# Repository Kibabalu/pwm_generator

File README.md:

# PWM power output generator

PWM power output generator for utilization in training arangements.

Generates a 0 to 100% duty cycle to the load at the output. The dyty cycle can be controlled by an potentiometer. Operating voltage 12VDC. Max. current 3A. In addition it features Inverse supply voltage protection and over-voltage protection. The board fits into a Hammond 1593K enclosure.

Most of PWM generator designs are based on 555 ICs. But I haven't found a circuit that covers up the full range from 0 to 100% duty cycle. Thus I used a more basic design: A combination of a Schmitt trigger and a Integrator, both implemented with two opamps (TLV2372), is feeding a comparator (TLV2372). The duty cycle of the resulting PWM signal is determind by the switching voltage comming from a potentiometer. A complementary driver, made by a NPN (BC817) and a PNP (BC807) transistor, drives a MOSFET (TSM900n06CW) for the load.

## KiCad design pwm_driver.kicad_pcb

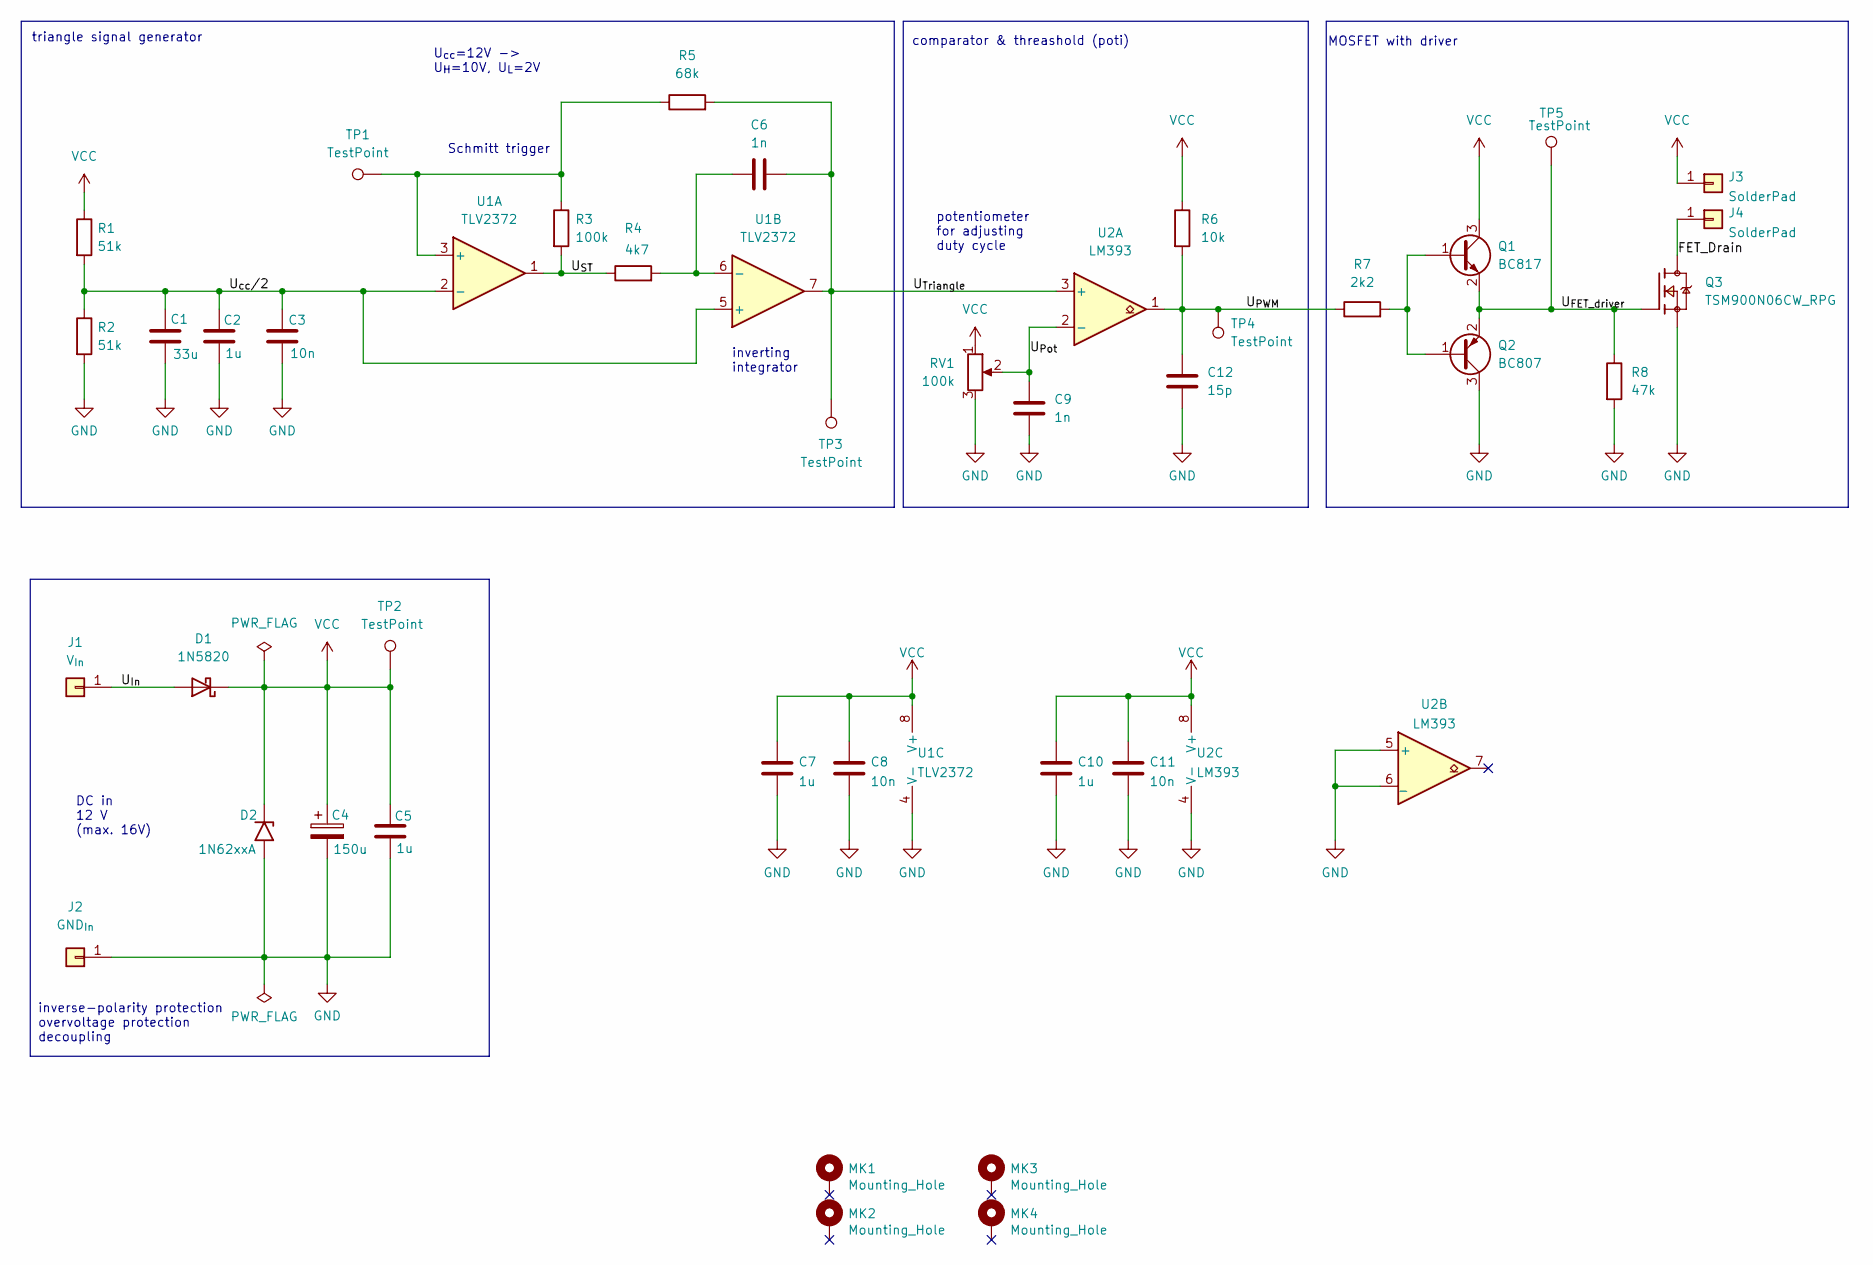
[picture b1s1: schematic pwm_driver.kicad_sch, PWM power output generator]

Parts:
C1: 33u; C_1206_3216Metric_Pad1.33x1.80mm_HandSolder
C2, C5, C7, C10: 1u; C_1206_3216Metric_Pad1.33x1.80mm_HandSolder
C3, C8, C11: 10n; C_1206_3216Metric_Pad1.33x1.80mm_HandSolder
C4: 150u; CP_Radial_D6.3mm_P2.50mm
C6, C9: 1n; C_1206_3216Metric_Pad1.33x1.80mm_HandSolder
C12: 15p; C_1206_3216Metric_Pad1.33x1.80mm_HandSolder
D1: 1N5820; D_DO-201AD_P15.24mm_Horizontal
D2: 1N62xxA; D_DO-201AE_P15.24mm_Horizontal
J1: V_{In}; SolderWirePad_1x01_SMD_5x10mm
J2: GND_{In}; SolderWirePad_1x01_SMD_5x10mm
J3, J4: SolderPad; SolderWirePad_1x01_SMD_5x10mm
MK1: Mounting_Hole; MountingHole_3.2mm_M3
MK2, MK3, MK4: Mounting_Hole; MountingHole_3.2mm_M3_ISO7380
Q1: BC817; SOT-23
Q2: BC807; SOT-23
Q3: TSM900N06CW_RPG; TRANS_TSM900N06CW_RPG; PARTREV D1706
R1, R2: 51k; R_1206_3216Metric_Pad1.30x1.75mm_HandSolder
R3: 100k; R_1206_3216Metric_Pad1.30x1.75mm_HandSolder
R4: 4k7; R_1206_3216Metric_Pad1.30x1.75mm_HandSolder
R5: 68k; R_1206_3216Metric_Pad1.30x1.75mm_HandSolder
R6: 10k; R_1206_3216Metric_Pad1.30x1.75mm_HandSolder
R7: 2k2; R_1206_3216Metric_Pad1.30x1.75mm_HandSolder
R8: 47k; R_1206_3216Metric_Pad1.30x1.75mm_HandSolder
RV1: 100k; PinHeader_1x03_P2.54mm_Vertical_SMD_Pin1Left
TP1, TP2, TP3, TP4, TP5: TestPoint; TestPoint_Pad_1.5x1.5mm
U1: TLV2372; SOIC-8_3.9x4.9mm_P1.27mm
U2: LM393; SOIC-8_3.9x4.9mm_P1.27mm

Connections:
/FET_Drain: J4.1, Q3.2, Q3.4
/U_{FET_driver}: Q1.2 (E), Q2.2 (E), Q3.1, R8.1, TP5.1
/U_{In}: D1.2 (A), J1.1
/U_{PWM}: C12.1, R6.2, R7.1, TP4.1, U2.1
/U_{Pot}: C9.1, RV1.2, U2.2 (-)
/U_{ST}: R3.2, R4.1, U1.1
/U_{Triangle}: C6.2, R5.2, TP3.1, U1.7, U2.3 (+)
/U_{cc}/2: C1.1, C2.1, C3.1, R1.2, R2.1, U1.2 (-), U1.5 (+)
GND: C1.2, C2.2, C3.2, C4.2, C5.2, C7.2, C8.2, C9.2, C10.2, C11.2, C12.2, D2.2 (A2), J2.1, Q2.3 (C), Q3.3, R2.2, R8.2, RV1.3, U1.4 (V-), U2.4 (V-), U2.5 (+), U2.6 (_)
unnamed: C6.1, R4.2, U1.6 (-)
unnamed: Q1.1 (B), Q2.1 (B), R7.2
unnamed: R3.1, R5.1, TP1.1, U1.3 (+)
VCC: C4.1, C5.1, C7.1, C8.1, C10.1, C11.1, D1.1 (K), D2.1 (A1), J3.1, Q1.3 (C), R1.1, R6.1, RV1.1, TP2.1, U1.8 (V+), U2.8 (V+)

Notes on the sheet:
Schmitt trigger
inverse-polarity protection overvoltage protection decoupling
comparator & threashold (poti)
U_{cc}=12V -> U_{H}=10V, U_{L}=2V
potentiometer for adjusting duty cycle
MOSFET with driver
triangle signal generator
DC in 12 V (max. 16V)
inverting integrator

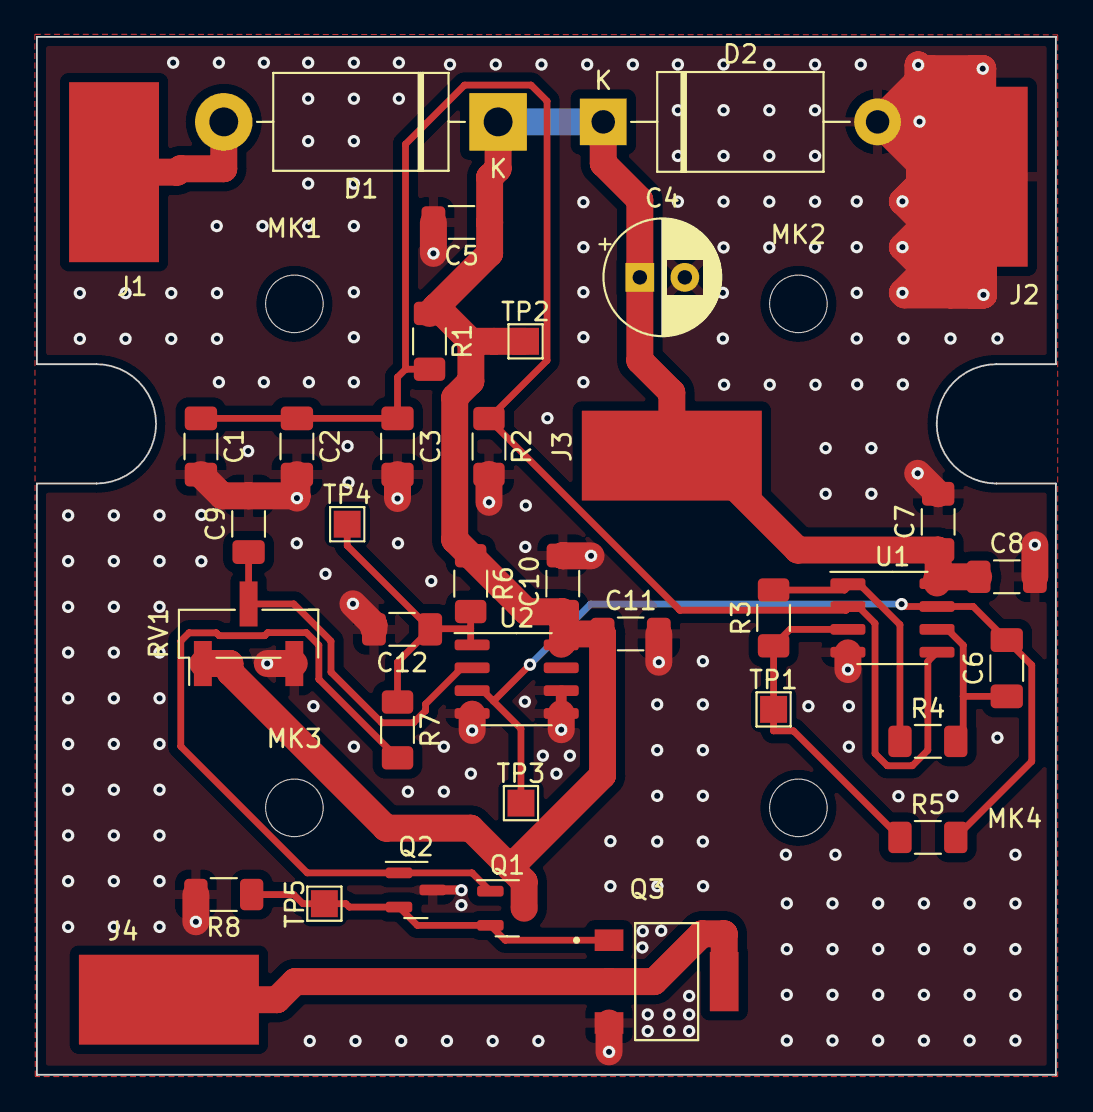
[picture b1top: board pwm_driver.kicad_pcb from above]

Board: 2 copper layers, 56.6 x 57.7 mm, 41 parts (0 on the bottom side), 13 nets.

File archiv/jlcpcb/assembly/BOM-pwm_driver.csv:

Comment,Designator,Footprint,LCSC
Mounting_Hole,MK1,MountingHole_3.2mm_M3,
Mounting_Hole,MK2,MountingHole_3.2mm_M3_ISO7380,
Mounting_Hole,MK3,MountingHole_3.2mm_M3_ISO7380,
Mounting_Hole,MK4,MountingHole_3.2mm_M3_ISO7380,
10k,R6,R_1206_3216Metric_Pad1.30x1.75mm_HandSolder,
1n,C6,C_1206_3216Metric_Pad1.33x1.80mm_HandSolder,
100k,R2,R_1206_3216Metric_Pad1.30x1.75mm_HandSolder,
1u,C7,C_1206_3216Metric_Pad1.33x1.80mm_HandSolder,
TestPoint,TP2,TestPoint_Pad_1.5x1.5mm,
BC807,Q2,SOT-23,
10u,C1,C_1206_3216Metric_Pad1.33x1.80mm_HandSolder,
TestPoint,TP3,TestPoint_Pad_1.5x1.5mm,
150u,C4,CP_Radial_D6.3mm_P2.50mm,
47k,R8,R_1206_3216Metric_Pad1.30x1.75mm_HandSolder,
10n,C8,C_1206_3216Metric_Pad1.33x1.80mm_HandSolder,
4k7,R4,R_1206_3216Metric_Pad1.30x1.75mm_HandSolder,
BC817,Q1,SOT-23,
SolderPad,J3,SolderWirePad_1x01_SMD_5x10mm,
2k2,R7,R_1206_3216Metric_Pad1.30x1.75mm_HandSolder,
10n,C10,C_1206_3216Metric_Pad1.33x1.80mm_HandSolder,
10n,C3,C_1206_3216Metric_Pad1.33x1.80mm_HandSolder,
GND_{In},J2,SolderWirePad_1x01_SMD_5x10mm,
1N62xxA,D2,D_DO-201AE_P15.24mm_Horizontal,
V_{In},J1,SolderWirePad_1x01_SMD_5x10mm,
SolderPad,J4,SolderWirePad_1x01_SMD_5x10mm,
100k,R1,R_1206_3216Metric_Pad1.30x1.75mm_HandSolder,
100k,RV1,PinHeader_1x03_P2.54mm_Vertical_SMD_Pin1Left,
TLV2372,U1,SOIC-8_3.9x4.9mm_P1.27mm,
1u,C2,C_1206_3216Metric_Pad1.33x1.80mm_HandSolder,
15p,C11,C_1206_3216Metric_Pad1.33x1.80mm_HandSolder,
BUK7880-55A,Q3,SOT-223-3_TabPin2,
1u,C5,C_1206_3216Metric_Pad1.33x1.80mm_HandSolder,
TestPoint,TP1,TestPoint_Pad_1.5x1.5mm,
TestPoint,TP4,TestPoint_Pad_1.5x1.5mm,
LM393,U2,SOIC-8_3.9x4.9mm_P1.27mm,
68k,R5,R_1206_3216Metric_Pad1.30x1.75mm_HandSolder,
100k,R3,R_1206_3216Metric_Pad1.30x1.75mm_HandSolder,
1N5820,D1,D_DO-201AD_P15.24mm_Horizontal,
1u,C9,C_1206_3216Metric_Pad1.33x1.80mm_HandSolder,
TestPoint,TP5,TestPoint_Pad_1.5x1.5mm,

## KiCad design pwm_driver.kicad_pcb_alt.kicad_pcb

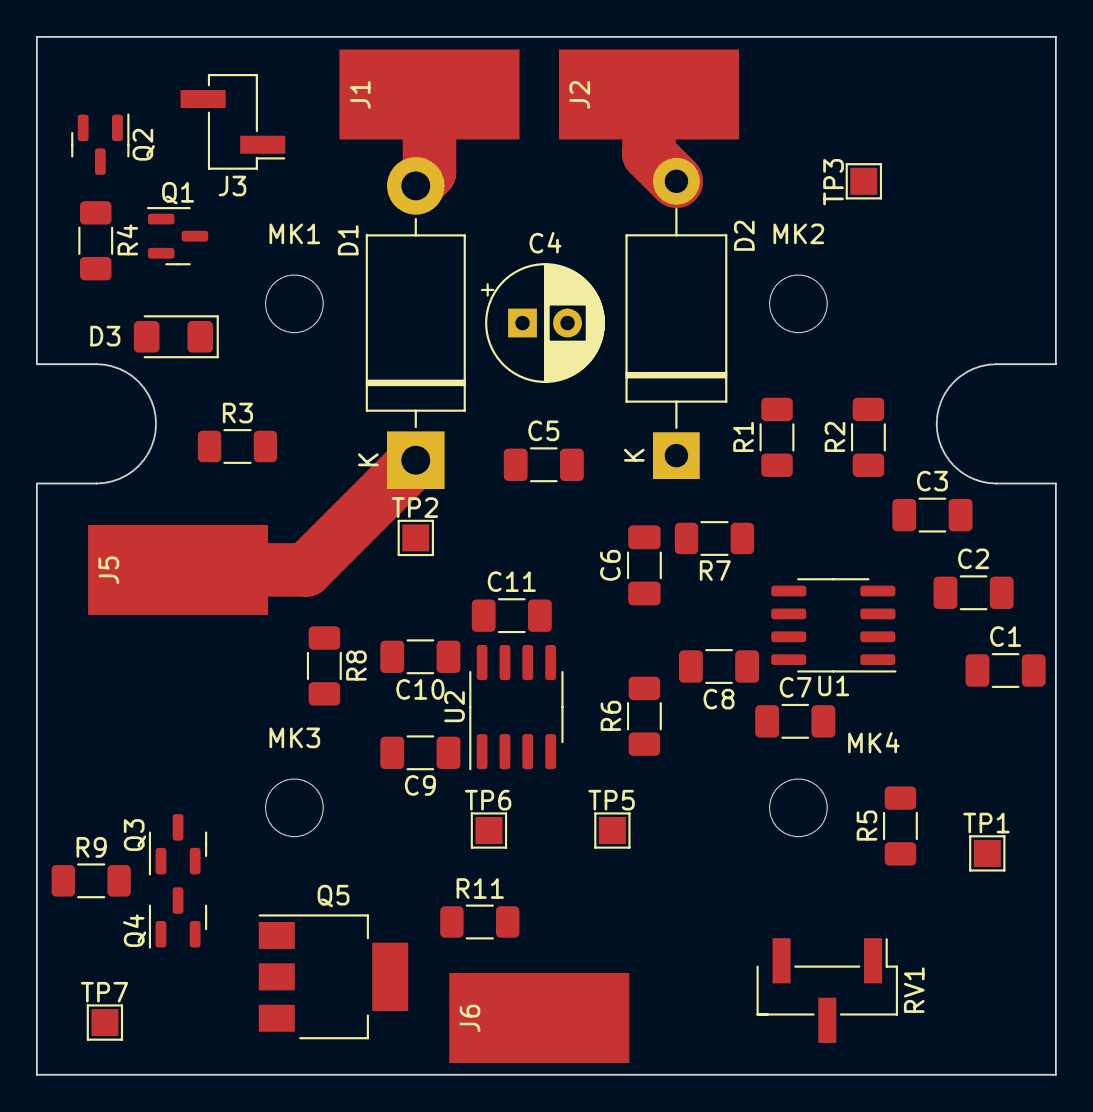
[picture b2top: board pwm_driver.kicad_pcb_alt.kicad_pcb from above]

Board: 2 copper layers, 56.6 x 57.7 mm, 47 parts (0 on the bottom side), 17 nets.

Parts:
C1: 10u; C_1206_3216Metric_Pad1.33x1.80mm_HandSolder
C2, C5, C7, C10: 1u; C_1206_3216Metric_Pad1.33x1.80mm_HandSolder
C3, C8, C11: 10n; C_1206_3216Metric_Pad1.33x1.80mm_HandSolder
C4: 150u; CP_Radial_D6.3mm_P2.50mm
C6: 1n; C_1206_3216Metric_Pad1.33x1.80mm_HandSolder
C9: 15p; C_1206_3216Metric_Pad1.33x1.80mm_HandSolder
D1: 1N5820; D_DO-201AD_P15.24mm_Horizontal
D2: 1N62xxA; D_DO-201AE_P15.24mm_Horizontal
D3: LED; LED_1206_3216Metric_Pad1.42x1.75mm_HandSolder
J1, J2, J5, J6: SolderPad; SolderWirePad_1x01_SMD_5x10mm
J3: Conn_01x02_Male; PinHeader_1x02_P2.54mm_Vertical_SMD_Pin1Left
MK1, MK2, MK3, MK4: Mounting_Hole; MountingHole_3.2mm_M3_ISO7380
Q1, Q2: BC847; SOT-23
Q3: BC817; SOT-23
Q4: BC807; SOT-23
Q5: BUK7880-55A; SOT-223-3_TabPin2
R1, R2, R5: 100k; R_1206_3216Metric_Pad1.30x1.75mm_HandSolder
R3, R6: 4k7; R_1206_3216Metric_Pad1.30x1.75mm_HandSolder
R4: 100; R_1206_3216Metric_Pad1.30x1.75mm_HandSolder
R7: 68k; R_1206_3216Metric_Pad1.30x1.75mm_HandSolder
R8: 10k; R_1206_3216Metric_Pad1.30x1.75mm_HandSolder
R9: 2k2; R_1206_3216Metric_Pad1.30x1.75mm_HandSolder
R11: 10R; R_1206_3216Metric_Pad1.30x1.75mm_HandSolder
RV1: 100k; PinHeader_1x03_P2.54mm_Vertical_SMD_Pin1Left
TP1, TP2, TP3, TP5, TP6, TP7: TestPoint; TestPoint_Pad_1.5x1.5mm
U1: TLV2372; SOIC-8_3.9x4.9mm_P1.27mm
U2: LM393; SOIC-8_3.9x4.9mm_P1.27mm

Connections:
/U_{FET_driver}: Q3.2 (E), Q4.2 (E), Q5.1 (G), R11.1, TP7.1
/U_{In}: D1.2 (A), J1.1
/U_{PWM}: C9.1, R8.2, R9.1, TP6.1, U2.1
/U_{Pot}: RV1.2, U2.2 (-)
/U_{ST}: R5.2, R6.1, U1.1
/U_{Triangle}: C6.2, R7.2, TP5.1, U1.7, U2.3 (+)
/U_{cc}/2: C1.1, C2.1, C3.1, R1.2, R2.1, U1.2 (-), U1.5 (+)
GND: C1.2, C2.2, C3.2, C4.2, C5.2, C7.2, C8.2, C9.2, C10.2, C11.2, D2.2 (A2), J2.1, Q1.2 (E), Q4.3 (C), Q5.3 (S), R2.2, R4.2, R11.2, RV1.3, TP3.1, U1.4 (V-), U2.4 (V-), U2.5 (+), U2.6 (_)
unnamed: C6.1, R6.2, U1.6 (-)
unnamed: D3.1 (K), J3.1
unnamed: J6.1, Q5.2 (D)
unnamed: Q1.1 (B), Q2.2 (E), R4.1
unnamed: Q1.3 (C), Q2.1 (B), R3.2
unnamed: J3.2, Q2.3 (C)
unnamed: Q3.1 (B), Q4.1 (B), R9.2
unnamed: R5.1, R7.1, TP1.1, U1.3 (+)
VCC: C4.1, C5.1, C7.1, C8.1, C10.1, C11.1, D1.1 (K), D2.1 (A1), D3.2 (A), J5.1, Q3.3 (C), R1.1, R3.1, R8.1, RV1.1, TP2.1, U1.8 (V+), U2.8 (V+)

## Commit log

2022-01-18 test commit
2022-01-18 1st commit
2022-01-18 some documentation
2022-01-19 export jlcpcb
2022-01-19 readme modified
2022-01-20 minor redesign (decoupling cap)
2022-01-21 pcb board 3d picture added
2022-02-03 subfolder with simulation model added
2022-02-03 some cleaning
2022-02-04 simulation model error fix
2022-02-04 cleaning
2022-02-05 some more simulation stuff
2022-02-05 added smoothing capacitor for potentiometer output, improved routing
2022-02-05 photo added from working device
2022-02-05 README.md edited
2022-02-06 documentation edited
2022-02-06 trace width modified for higher currents
2022-02-06 minor layout modifications
2022-02-06 new §D rendering
2022-02-06 some more GND vias added
